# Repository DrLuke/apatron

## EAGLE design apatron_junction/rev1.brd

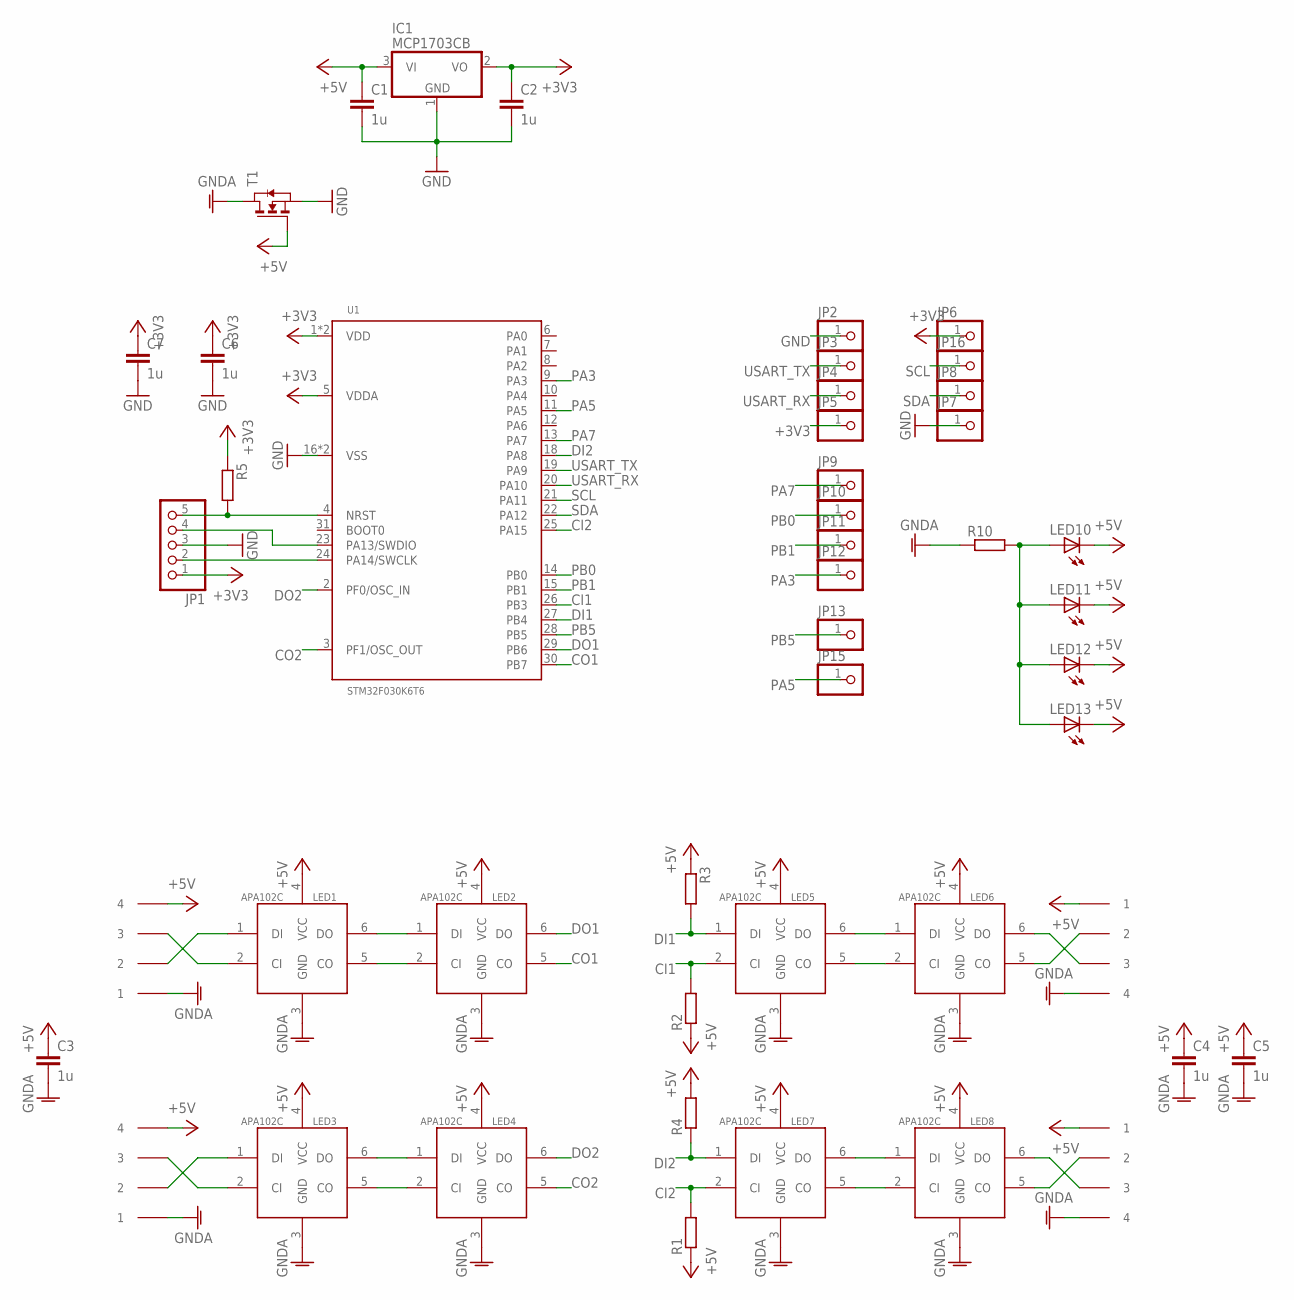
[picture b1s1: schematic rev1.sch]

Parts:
C1, C2, C3, C4, C5, C6, C7: 1u; C0603
IC1: MCP1703CB; SOT23
JP1: PINHD-1X5; 1X05
JP2, JP3, JP4, JP5, JP6, JP7, JP8, JP9, JP10, JP11, JP12, JP13, JP15, JP16: PINHD-1X1; 1X01
LED1, LED2, LED3, LED4, LED5, LED6, LED7, LED8: APA102C; RGBLED5050
LED10, LED11, LED12, LED13: LEDSML0603; SML0603
R1, R2, R3, R4, R5, R10: RR0603; R0603
T1: NMOSSOT23-6; SOT23-6
U1: STM32F030K6T6; LQFP-32
U$1, U$2, U$3, U$4: JSTPH

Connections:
+3V3: C2.1, C6.1, C7.1, IC1.2 (VO), JP1.1, JP5.1, JP6.1, R5.1, U1.1 (VDD), U1.5 (VDDA), U1.17 (VDD)
+5V: C1.1, C3.1, C4.1, C5.1, IC1.3 (VI), LED1.4 (VCC), LED2.4 (VCC), LED3.4 (VCC), LED4.4 (VCC), LED5.4 (VCC), LED6.4 (VCC), LED7.4 (VCC), LED8.4 (VCC), LED10.C, LED11.C, LED12.C, LED13.C, R1.1, R2.1, R3.1, R4.2, T1.3 (G), U$1.P$4 (4), U$2.P$4 (4), U$3.1, U$4.1
CI1: LED5.2 (CI), R2.2, U1.26 (PB3)
CI2: LED7.2 (CI), R1.2, U1.25 (PA15)
CI-CON1: LED1.2 (CI), U$1.P$3 (3)
CI-CON2: LED3.2 (CI), U$2.P$3 (3)
CO1: LED2.5 (CO), U1.30 (PB7)
CO2: LED4.5 (CO), U1.3 (PF1/OSC_OUT)
DI1: LED5.1 (DI), R3.2, U1.27 (PB4)
DI2: LED7.1 (DI), R4.1, U1.18 (PA8)
DI-CON1: LED1.1 (DI), U$1.P$2 (2)
DI-CON2: LED3.1 (DI), U$2.P$2 (2)
DO1: LED2.6 (DO), U1.29 (PB6)
DO2: LED4.6 (DO), U1.2 (PF0/OSC_IN)
GND: C1.2, C2.2, C6.2, C7.2, IC1.1 (GND), JP1.3, JP2.1, JP7.1, T1.4 (S), U1.16 (VSS), U1.32 (VSS)
GNDA: C3.2, C4.2, C5.2, LED1.3 (GND), LED2.3 (GND), LED3.3 (GND), LED4.3 (GND), LED5.3 (GND), LED6.3 (GND), LED7.3 (GND), LED8.3 (GND), R10.1, T1.1 (D), T1.2 (D), T1.5 (D), T1.6 (D), U$1.1, U$2.1, U$3.P$4 (4), U$4.P$4 (4)
unnamed: LED7.6 (DO), LED8.1 (DI)
unnamed: LED7.5 (CO), LED8.2 (CI)
unnamed: LED1.6 (DO), LED2.1 (DI)
unnamed: LED1.5 (CO), LED2.2 (CI)
unnamed: LED3.5 (CO), LED4.2 (CI)
unnamed: LED3.6 (DO), LED4.1 (DI)
unnamed: LED5.6 (DO), LED6.1 (DI)
unnamed: LED5.5 (CO), LED6.2 (CI)
unnamed: LED6.6 (DO), U$4.P$3 (3)
unnamed: LED6.5 (CO), U$4.P$2 (2)
unnamed: LED8.6 (DO), U$3.P$3 (3)
unnamed: LED8.5 (CO), U$3.P$2 (2)
unnamed: LED10.A, LED11.A, LED12.A, LED13.A, R10.2
NRST: JP1.5, R5.2, U1.4 (NRST)
PA3: JP12.1, U1.9 (PA3)
PA5: JP15.1, U1.11 (PA5)
PA7: JP9.1, U1.13 (PA7)
PB0: JP10.1, U1.14 (PB0)
PB1: JP11.1, U1.15 (PB1)
PB5: JP13.1, U1.28 (PB5)
SCL: JP16.1, U1.21 (PA11)
SDA: JP8.1, U1.22 (PA12)
SWCLOCK: JP1.2, U1.24 (PA14/SWCLK)
SWDIO: JP1.4, U1.23 (PA13/SWDIO)
USART_RX: JP4.1, U1.20 (PA10)
USART_TX: JP3.1, U1.19 (PA9)

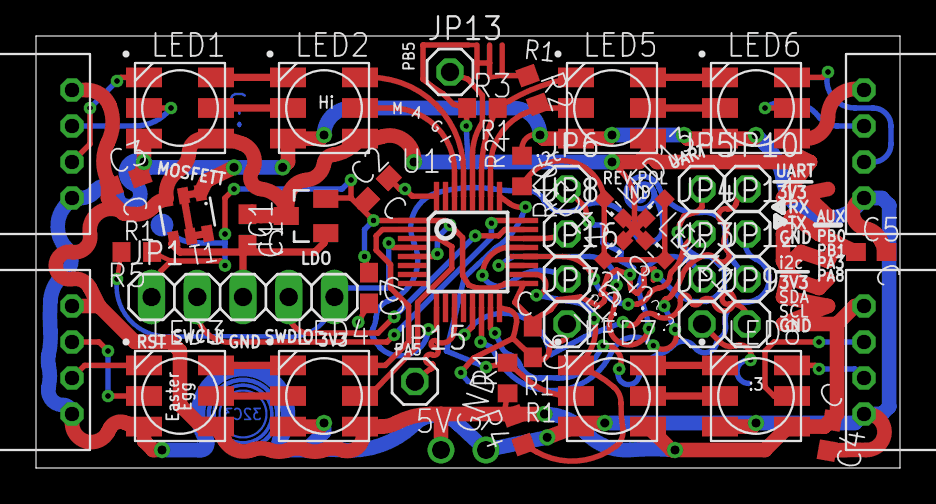
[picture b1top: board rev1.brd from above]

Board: 2 copper layers, 48.0 x 24.0 mm, 47 parts (0 on the bottom side), 42 nets.

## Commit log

2015-11-10 Rev1 of junction board
2015-11-17 Rev1 production
2015-11-17 Add gerbers
